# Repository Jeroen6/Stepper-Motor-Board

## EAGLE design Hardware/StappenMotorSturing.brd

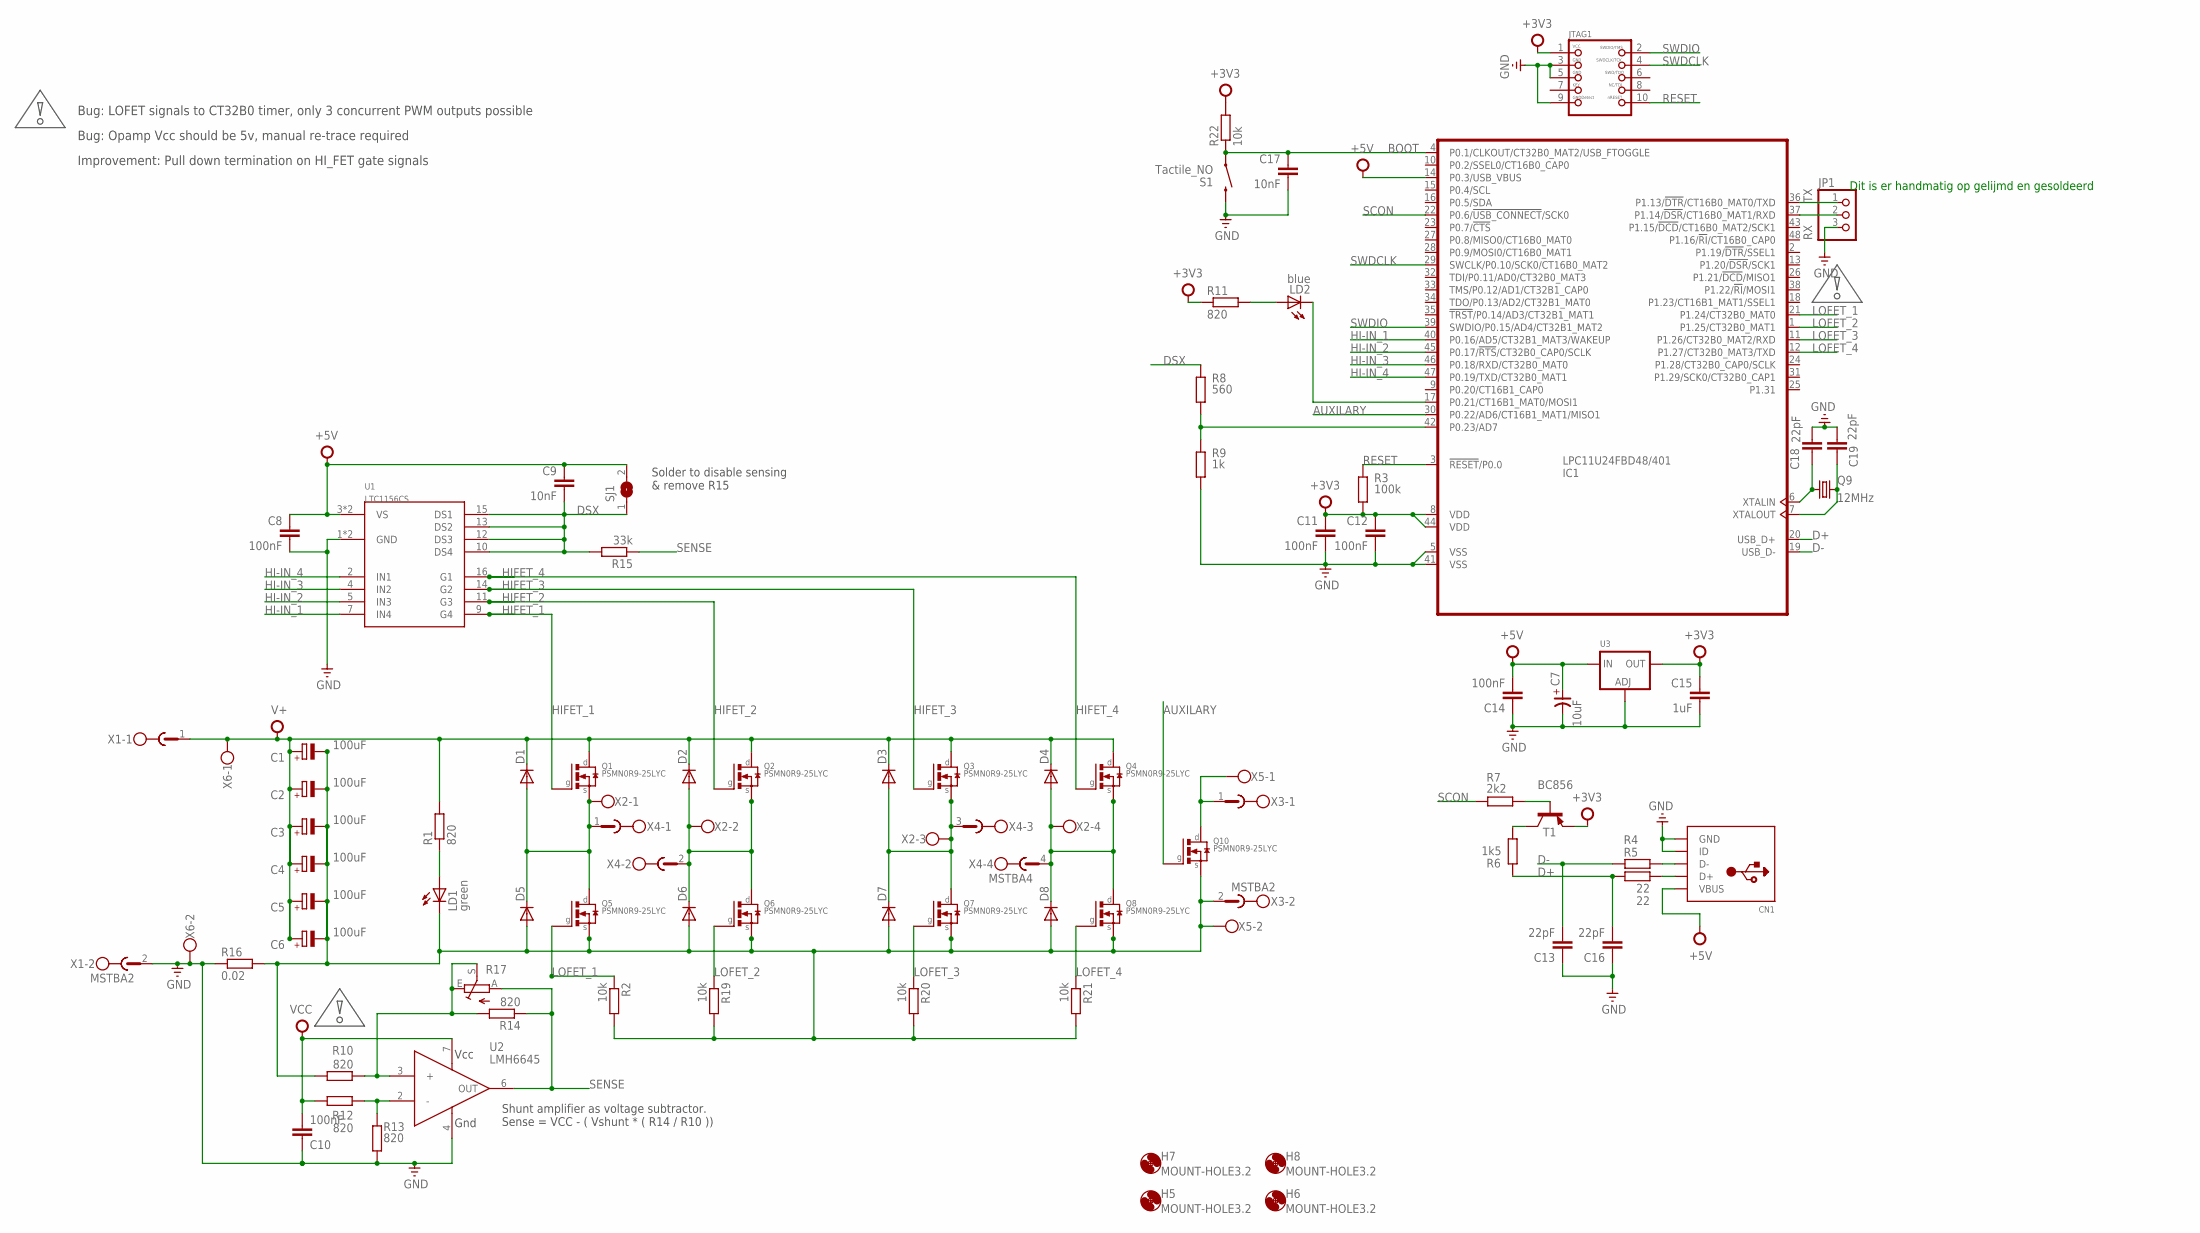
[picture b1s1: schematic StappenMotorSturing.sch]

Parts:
C1, C2, C3, C4, C5, C6: 100uF; E2,5-7
C7: 10uF; 3216-18W/T
C8, C10, C11, C12, C14: 100nF; C0805
C9, C17: 10nF; C0805
C13, C16, C18, C19: 22pF; C0805
C15: 1uF; C0805
CN1: USBMINIB; USB-MINIB
D1, D2, D3, D4, D5, D6, D7, D8: DIODE-SOD80C; SOD80C
H5, H6, H7, H8: MOUNT-HOLE3.2; 3,2
IC1: LPC11U24FBD48/401; LQFP48
JP1: HEADER-1X3; 1X03_OVAL
JTAG1: JTAG-CORTEXM3; 2X05_1.27MM_SMT
LD1: green; CHIP-LED0805
LD2: blue; CHIP-LED0805
Q1, Q2, Q3, Q4, Q5, Q6, Q7, Q8, Q10: PSMN0R9-25LYC; SOT669
Q9: 12MHz; CRYSTAL-SMD-5X3
R1, R10, R11, R12, R13, R14: 820; R0805
R2, R19, R20, R21, R22: 10k; R0805
R3: 100k; R0805
R4, R5: 22; R0805
R6: 1k5; R0805
R7: 2k2; R0805
R8: 560; R0805
R9: 1k; R0805
R15: 33k; R0805
R16: 0.02; R2512
R17: TRIM_EU-RS3; RS3
S1: Tactile_NO; SPARKFUN_TACTILE_MINI
SJ1: SJ
T1: BC856; SOT23-BEC
U1: LTC1156CS; SOL16
U2: LMH6645; SOIC8
U3: LM1117SOT223-WAVE; SOT223-W
X1, X3: MSTBA2
X2: W237-4
X4: MSTBA4
X5, X6: W237-102

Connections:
+3V3: C11.1, C12.1, C15.1, IC1.8 (VDD), IC1.44 (VDD), JTAG1.1, R3.2, R11.1, R22.2, T1.E, U3.2 (OUT)
+5V: C7.+, C8.1, C9.1, C14.2, CN1.VBUS, IC1.14 (P0.3/USB_VBUS), SJ1.2, U1.3 (VS), U1.8 (VS), U3.3 (IN)
AUX+: Q10.5 (D), X3.1, X5.1
AUXILARY: IC1.30 (P0.22/AD6/CT16B1_MAT1/MISO1), Q10.4 (G)
BOOT: C17.1, IC1.4 (P0.1/CLKOUT/CT32B0_MAT2/USB_FTOGGLE), R22.1, S1.P$1 (1)
D+: C16.1, IC1.20 (USB_D+), R5.1, R6.1
D-: C13.2, IC1.19 (USB_D-), R4.1
DSX: C9.2, R8.1, R15.2, SJ1.1, U1.10 (DS4), U1.12 (DS3), U1.13 (DS2), U1.15 (DS1)
GND: C7.-, C8.2, C10.1, C11.2, C12.2, C13.1, C14.1, C15.2, C16.2, C17.2, C18.1, C19.1, CN1.GND, CN1.ID, IC1.5 (VSS), IC1.41 (VSS), JP1.3, JTAG1.3, JTAG1.5, JTAG1.9, R9.2, R13.2, R16.1, S1.P$2 (2), U1.1 (GND), U1.6 (GND), U2.4 (GND), U3.1 (ADJ), X1.2, X6.2
HI-IN_1: IC1.40 (P0.16/AD5/CT32B1_MAT3/WAKEUP), U1.7 (IN4)
HI-IN_2: IC1.45 (P0.17/!RTS!/CT32B0_CAP0/SCLK), U1.5 (IN3)
HI-IN_3: IC1.46 (P0.18/RXD/CT32B0_MAT0), U1.4 (IN2)
HI-IN_4: IC1.47 (P0.19/TXD/CT32B0_MAT1), U1.2 (IN1)
HIFET_1: Q1.4 (G), U1.9 (G4)
HIFET_2: Q2.4 (G), U1.11 (G3)
HIFET_3: Q3.4 (G), U1.14 (G2)
HIFET_4: Q4.4 (G), U1.16 (G1)
LOFET_1: IC1.21 (P1.24/CT32B0_MAT0), Q5.4 (G), R2.1
LOFET_2: IC1.1 (P1.25/CT32B0_MAT1), Q6.4 (G), R19.1
LOFET_3: IC1.11 (P1.26/CT32B0_MAT2/RXD), Q7.4 (G), R20.1
LOFET_4: IC1.12 (P1.27/CT32B0_MAT3/TXD), Q8.4 (G), R21.1
unnamed: R10.1, R14.2, R17.E, R17.S, U2.3 (+)
unnamed: D1.A, D5.C, Q1.1 (S), Q1.2 (S), Q1.3 (S), Q5.5 (D), X2.1, X4.1
unnamed: D2.A, D6.C, Q2.1 (S), Q2.2 (S), Q2.3 (S), Q6.5 (D), X2.2, X4.2
unnamed: LD2.A, R11.2
unnamed: D4.A, D8.C, Q4.1 (S), Q4.2 (S), Q4.3 (S), Q8.5 (D), X2.4, X4.4
unnamed: D3.A, D7.C, Q3.1 (S), Q3.2 (S), Q3.3 (S), Q7.5 (D), X2.3, X4.3
unnamed: R12.1, R13.1, U2.2 (-)
unnamed: IC1.17 (P0.21/CT16B1_MAT0/MOSI1), LD2.C
unnamed: C1.-, C2.-, C3.-, C4.-, C5.-, C6.-, D5.A, D6.A, D7.A, D8.A, LD1.C, Q5.1 (S), Q5.2 (S), Q5.3 (S), Q6.1 (S), Q6.2 (S), Q6.3 (S), Q7.1 (S), Q7.2 (S), Q7.3 (S), Q8.1 (S), Q8.2 (S), Q8.3 (S), Q10.3 (S), R2.2, R10.2, R16.2, R19.2, R20.2, R21.2, X3.2, X5.2
unnamed: LD1.A, R1.1
unnamed: CN1.D+, R5.2
unnamed: CN1.D-, R4.2
unnamed: R6.2, T1.C
unnamed: R7.2, T1.B
unnamed: C18.2, IC1.6 (XTALIN), Q9.1
unnamed: C19.2, IC1.7 (XTALOUT), Q9.3 (2)
unnamed: IC1.42 (P0.23/AD7), R8.2, R9.1
RESET: IC1.3 (!RESET!/P0.0), JTAG1.10, R3.1
RX: IC1.37 (P1.14/!DSR!/CT16B0_MAT1/RXD), JP1.2
SCON: IC1.22 (P0.6/!USB_CONNECT!/SCK0), R7.1
SENSE: R14.1, R15.1, R17.A, U2.6 (OUT)
SWDCLK: IC1.29 (SWCLK/P0.10/SCK0/CT16B0_MAT2), JTAG1.4
SWDIO: IC1.39 (SWDIO/P0.15/AD4/CT32B1_MAT2), JTAG1.2
TX: IC1.36 (P1.13/!DTR!/CT16B0_MAT0/TXD), JP1.1
V+: C1.+, C2.+, C3.+, C4.+, C5.+, C6.+, D1.C, D2.C, D3.C, D4.C, Q1.5 (D), Q2.5 (D), Q3.5 (D), Q4.5 (D), R1.2, X1.1, X6.1
VCC: C10.2, R12.2, U2.7 (VCC)

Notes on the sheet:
Shunt amplifier as voltage subtractor. Sense = VCC - ( Vshunt * ( R14 / R10 ))
Solder to disable sensing & remove R15
Bug: Opamp Vcc should be 5v, manual re-trace required
Bug: LOFET signals to CT32B0 timer, only 3 concurrent PWM outputs possible
Improvement: Pull down termination on HI_FET gate signals
Dit is er handmatig op gelijmd en gesoldeerd

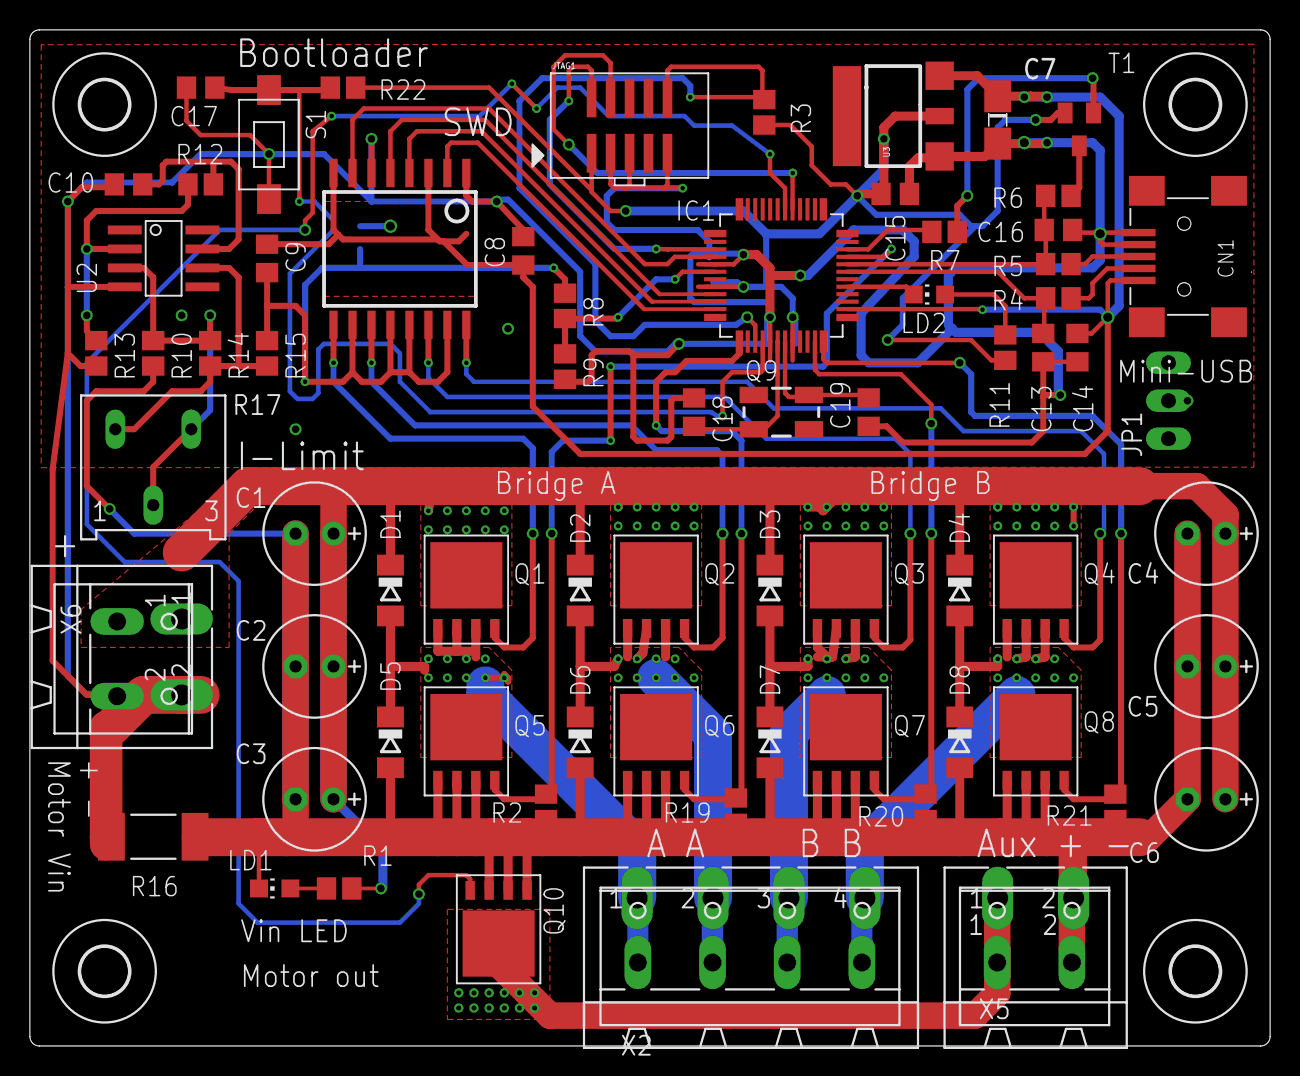
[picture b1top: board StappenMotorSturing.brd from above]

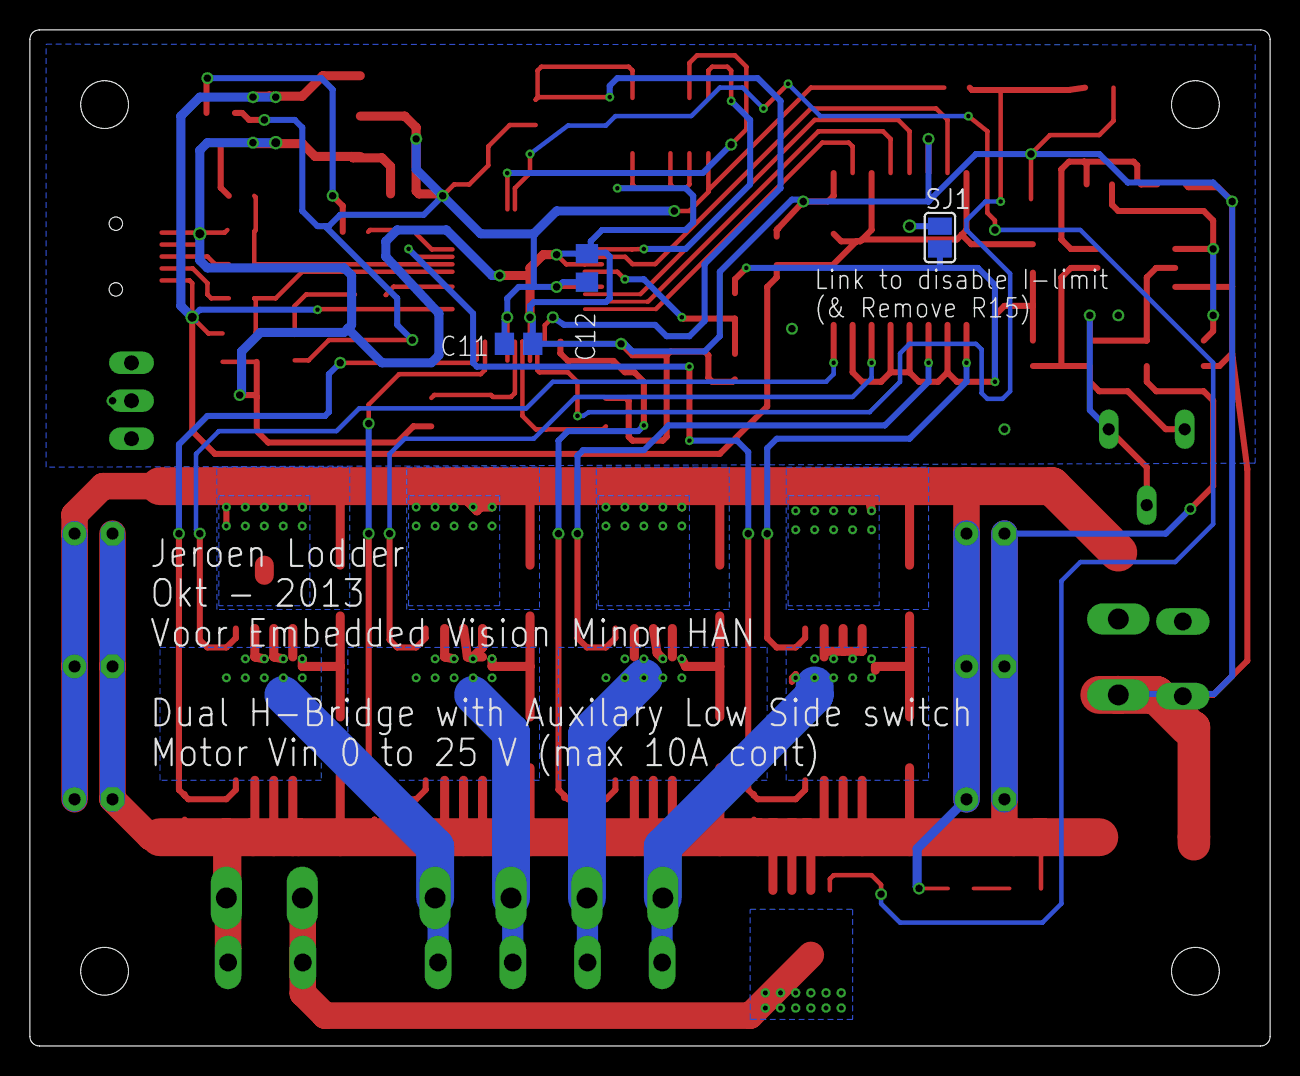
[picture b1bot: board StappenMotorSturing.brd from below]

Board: 2 copper layers, 83.0 x 68.0 mm, 80 parts (3 on the bottom side), 47 nets.

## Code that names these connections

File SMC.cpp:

/**
 * @file    SMC.cpp
 * @brief   Stepper motor control module uses 1/8 microstepping
 *
 * @author	Jeroen Lodder
 * @date		Oktober 2013
 *
 * @{
 */
#include "mbed.h"
#include "smc.h"
#include "CT32B0_PWM.h"

#define PWM_PERIOD				513		/**< @brief PWM period integer */
#define MIN_STEPTIME_US  	100   /**< @brief Minimum time required for one microstep, derived from Hi-side driver latency (in uS) */

/* Motor Control IO */
DigitalOut HIFET_1(P0_16);	/**< @brief Hi Side FET 1 of bridge 1 */
DigitalOut HIFET_2(P0_17);  /**< @brief Hi Side FET 2 of bridge 1 */
DigitalOut HIFET_3(P0_18);  /**< @brief Hi Side FET 3 of bridge 2 */
DigitalOut HIFET_4(P0_19);  /**< @brief Hi Side FET 4 of bridge 2 */

/* Motor Control stepcontrol */
Ticker smc;
volatile static int smc_walker		=	0;	/**< @brief Motor control LUT index */
volatile static int smc_dir 			= 1; 	/**< @brief Director in lookup table (unused) */
volatile static int smc_steps			= -1; /**< @brief Remaining steps */
volatile static int smc_free			= 1;  /**< @brief Argument to free motor when done */
volatile static int smc_abort			= 0;  /**< @brief Set when motor control should quit by itself */
volatile static int smc_steptime 	= 0;  /**< @brief Time used to make 1 step */
volatile static int smc_isPaused 	= 0;  /**< @brief Boolean for paused state of control */

/**
 * @brief   Initializes Stepper Motor Control
 */
void SMC_init(void){
	// Hi fet low
  HIFET_1 = 0;
	HIFET_2 = 0;
	HIFET_3 = 0;
	HIFET_4 = 0;
	// Wait minimum
	
	// Lo fet low
  CT32B0_initpwm(PWM_PERIOD,0);
	// Start pwm
	CT32B0_start();
}

/**
 * @brief   De-Initializes Stepper Motor Control
 */
void SMC_deinit(void){
	smc.detach();
	CT32B0_deinit(0);
	
  HIFET_1 = 0;
	HIFET_2 = 0;
	HIFET_3 = 0;
	HIFET_4 = 0;

	smc_walker	=	0;
	smc_dir 		= 1;
	smc_steps	= -1;
	smc_free		= 1;
  smc_abort	= 0;
	smc_isPaused = 0;
}

/**
 * @brief   Routine called by interrupt to modify H-Bridge states
 */
void SMC_routine(void){
	#define i	smc_walker
	CT32B0_wait_refresh();
	__disable_irq();
	// Phase 1 A	
	// If sin +, H1->L2
	// If sin -, H2->L1
	// If direction -1, swap motor A channels, this changes direction.
	// Reversing lookup table is not effective
	
	if(smc_dir > 0){
		HIFET_1 = LUT_H1[i];
		HIFET_2 = LUT_H2[i];
		if(LUT_L1[i] == 0)
			CT32B0_set(0, (PWM_PERIOD+1) );
		else
			CT32B0_set(0, PWM_PERIOD-LUT_L1[i] );
		if(LUT_L2[i] == 0)
			CT32B0_set(1, (PWM_PERIOD+1) );
		else
			CT32B0_set(1, PWM_PERIOD-LUT_L2[i] );
	}else{
		// Reversed for dir -1
		HIFET_1 = LUT_H2[i];
		HIFET_2 = LUT_H1[i];
		if(LUT_L2[i] == 0)
			CT32B0_set(0, (PWM_PERIOD+1) );
		else
			CT32B0_set(0, PWM_PERIOD-LUT_L2[i] );
		if(LUT_L1[i] == 0)
			CT32B0_set(1, (PWM_PERIOD+1) );
		else
			CT32B0_set(1, PWM_PERIOD-LUT_L1[i] );
	}

	// Phase 1 A	
	// If sin +, H1->L2
	// If sin -, H2->L1
	HIFET_3 = LUT_H3[i]; 
	HIFET_4 = LUT_H4[i]; 
	if(LUT_L3[i] == 0)
		CT32B0_set(2, (PWM_PERIOD+1) );
	else
		CT32B0_set(2, PWM_PERIOD-LUT_L3[i] );
	if(LUT_L4[i] == 0)
		CT32B0_set(3, (PWM_PERIOD+1) );
	else
		CT32B0_set(3, PWM_PERIOD-LUT_L4[i] );
	if(i==9)
		CT32B0_stage(1);
	if(i==24)
		CT32B0_stage(0);
	CT32B0_reload_mat();	
	
	/*
	volatile static uint8_t hifet[4] = {0,0,0,0};
	hifet[0] = HIFET_1;
	hifet[1] = HIFET_2;
	hifet[2] = HIFET_3;
	hifet[3] = HIFET_4;
	volatile static uint8_t lofet[4] = {0,0,0,0};
	if(LUT_L1[i])	lofet[0] = 1; else lofet[0] = 0;
	if(LUT_L2[i])	lofet[1] = 1; else lofet[1] = 0;
	if(LUT_L3[i])	lofet[2] = 1; else lofet[2] = 0;
	if(LUT_L4[i])	lofet[3] = 1; else lofet[3] = 0;
	volatile static uint8_t errfet[4] = {0,0,0,0};
	errfet[0] = hifet[0] & lofet[0];
	errfet[1] = hifet[1] & lofet[1];
	errfet[2] = hifet[2] & lofet[2];
	errfet[3] = hifet[3] & lofet[3];
	
	if( errfet[0] | errfet[1] | errfet[2] | errfet[3] ){
		// ILLEGAL MODE
	//	smc_abort = 1;
		 __NOP();
	} */
	
	#undef i
	
	/* Walk */
	smc_walker += 1; //abs(smc_dir);
	if(smc_walker > 31)
	smc_walker = 0;
	//if(smc_walker < 0)
	//smc_walker = 31;
	/* Coutdown */
	if(smc_steps != -1){
		if(smc_steps == 0 || smc_abort == 1){
			if(smc_free || smc_abort == 1){
				// motor free
				HIFET_1 = 0;
				HIFET_2 = 0;
				HIFET_3 = 0;
				HIFET_4 = 0;
				CT32B0_deinit(0);
			}else{
				// motor locked
			}
			smc.detach();
			smc_abort = 0;
			smc_isPaused = 0;
		}
	smc_steps--;
	}
	__enable_irq();
}

/**
 * @brief   Stepper motor control main command
 *
 * @param[in] 	steps			Number of steps to take
 * @param[in] 	dir			  Direction to step in, 1 or 0
 * @param[in] 	time_ms	  Time to take for these steps
 * @param[in] 	free	    Free or lock motor when done 1 or 0 respectively
 * @return			-1 when illegal command or mode	 
 */
int SMC_step(int steps, uint8_t dir, uint32_t time_ms, uint8_t free){
	// steps   = number of microsteps (8 microsteps per full step)
	// dir	   = -1 or 1
	// time_us = completion time in s
	uint32_t steptime = (time_ms*1000)/steps;	
	// Parameter check
	if(smc_steps != -1)	return -1;	// Only if motor idle
	if(steps < 1) return -1;        // At least one step
	if(dir) dir = 1;            		// Round dir to bool
	if(free) free = 1;        			// Round free to bool
	if(steptime < MIN_STEPTIME_US)  // Verify steptime
			return -1;
	if(dir == 0) 
		smc_dir = -1; 
	else 
		smc_dir = 1;
	// Configure stepper
	smc_steps = steps;
	smc_free	= free;
	smc_steptime = steptime;
	smc_isPaused = 0;
	// Initiate
	SMC_init();				
	smc.attach_us(&SMC_routine, smc_steptime);
	return 0;	
}

/**
 * @brief   Return 1 of stepper motor control is idle
 */
uint32_t SMC_idle(void){
	if(smc_steps == -1)
		return 1;
	else
		return 0;
}

/**
 * @brief   Puts motor in brake mode, enable all low-side mosfets
 */
void SMC_brake(void){
	// Do not brake when active control
	if(smc_walker > 0)
		return;
	// Regular deinit
	SMC_deinit();
	// Re-enable low side
	CT32B0_deinit(1);
}

/**
 * @brief   Puts motor in free mode, disables all mosfets
 */
void SMC_free(void){
	// Do not free when active control
	if(smc_walker > 0)
		return;
	// Regular deinit
	SMC_deinit();
	// Re-enable low side
	CT32B0_deinit(0);
}

/**
 * @brief   Pause current stepping command
 */
void SMC_pause(void){
	if( !SMC_idle() ){
		smc.detach();
		smc_isPaused = 1;
	}
}

/**
 * @brief   Continue from pause
 */
void SMC_continue(void){
	if( !SMC_idle() && smc_isPaused==1 ){
		smc.attach_us(&SMC_routine, smc_steptime);
		smc_isPaused = 0;
	}
}

/**
 * @brief   Return remaining steps, negative if paused
 */
int SMC_getState(void){
	if( smc_steps < 0 ){
		return 0;
	}else{
	  if(smc_isPaused)
			return (-1*smc_steps);
		else
		  return (1*smc_steps);
	}
}

/**
* @brief   Egg, open it to find out
*/
void SMC_egg(void){
const	uint16_t rr[] = {
		627  ,		1045 ,
		122  , 		785  ,
		887  , 		187  ,
		233  ,		166  ,
		788  , 		752  ,
		1157
	};
	int rri=0;
	// Egg
	for(int i=0;i<2; i++){
		SMC_step(rr[rri++]	, 1, 685, 1);		// 83 - 987
		while( !SMC_idle()) ;       //    -
		wait_ms(1);
		SMC_step(rr[rri++]	, 1, 965, 1);	// 85 - 1108
		while( !SMC_idle()) ;       //    -
		wait_ms(1);
		SMC_step(rr[rri++]	, 1, 245, 1);   // 78 - 739
		while( !SMC_idle()) ;       //    -
		wait_ms(1);
		SMC_step(rr[rri++]	, 1, 725, 1);   // 85 - 1108
		while( !SMC_idle()) ;       //    -
		wait_ms(1);
		SMC_step(rr[rri++]	, 1, 710, 1);   // 87 - 1244
		while( !SMC_idle()) ;       //    -
		wait_ms(1);
		SMC_step(rr[rri++]	, 1, 125, 1);   // 90 - 1479
		while( !SMC_idle()) ;       //    -
		wait_ms(1);
		SMC_step(rr[rri++]	, 1, 175, 1);   // 88 - 1318
		while( !SMC_idle()) ;       //    -
		wait_ms(1);
		SMC_step(rr[rri++]	, 1, 133, 1);   // 87 - 1244
		while( !SMC_idle()) ;       //    -
		wait_ms(1);
		SMC_step(rr[rri++]	, 1, 860, 1);   // 83 - 987
		while( !SMC_idle()) ;       //    -
		wait_ms(1);
		SMC_step(rr[rri++]	, 1, 695, 1);   // 85 - 1108
		while( !SMC_idle()) ;       //    -
		wait_ms(1);
		SMC_step(rr[rri++]	, 1, 2315, 1); // 78 -  739
		while( !SMC_idle()) ;       //    -
		wait_ms(1);
		rri=0;
	}
}
/**
 *@}
 */

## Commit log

2013-10-18 Initial
2013-10-18 Initial with libs
2013-10-19 Blinky working with HID
2013-10-19 Stepper motor running
2013-10-20 Basic usb api
2013-10-20 Added stop command
2013-10-23 New USB api. Not fully functional yet
2013-10-24 Working auxilary. Issue with motor control direction = 0; Api extended.
2013-10-24 Fix dir=0 issue
2013-10-24 Reasonably complete
2013-10-26 Source cleanup, Doxygen, and reduced some glitching issue when asked for motor state too much.
2013-10-27 Some more cleanup
2013-10-28 Fix aux disable after a while.
2013-10-29 More doxygen and include case fix
2013-10-29 Added Hardware and Schematic (eagle 6.4)
2013-10-30 fix led blink after soft reset
2013-10-31 Added signature to binary to validate .bin for USB MSC Bootloader
2013-10-31 Firmware Version 3
2014-01-23 Added UART header, routed with airwire
2014-01-23 Added UART control. Identical protocol as USB.
2014-01-23 Additional files for testing and documenting
2014-01-23 Add bootloader guide

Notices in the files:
parts and their libraries:
microbuilder: This work is placed in the public domain, and may be freely used for commercial and non-commercial work with the following conditions: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
SparkFun: Licensing: CC v3.0 Share-Alike You are welcome to use this library for commercial purposes.
